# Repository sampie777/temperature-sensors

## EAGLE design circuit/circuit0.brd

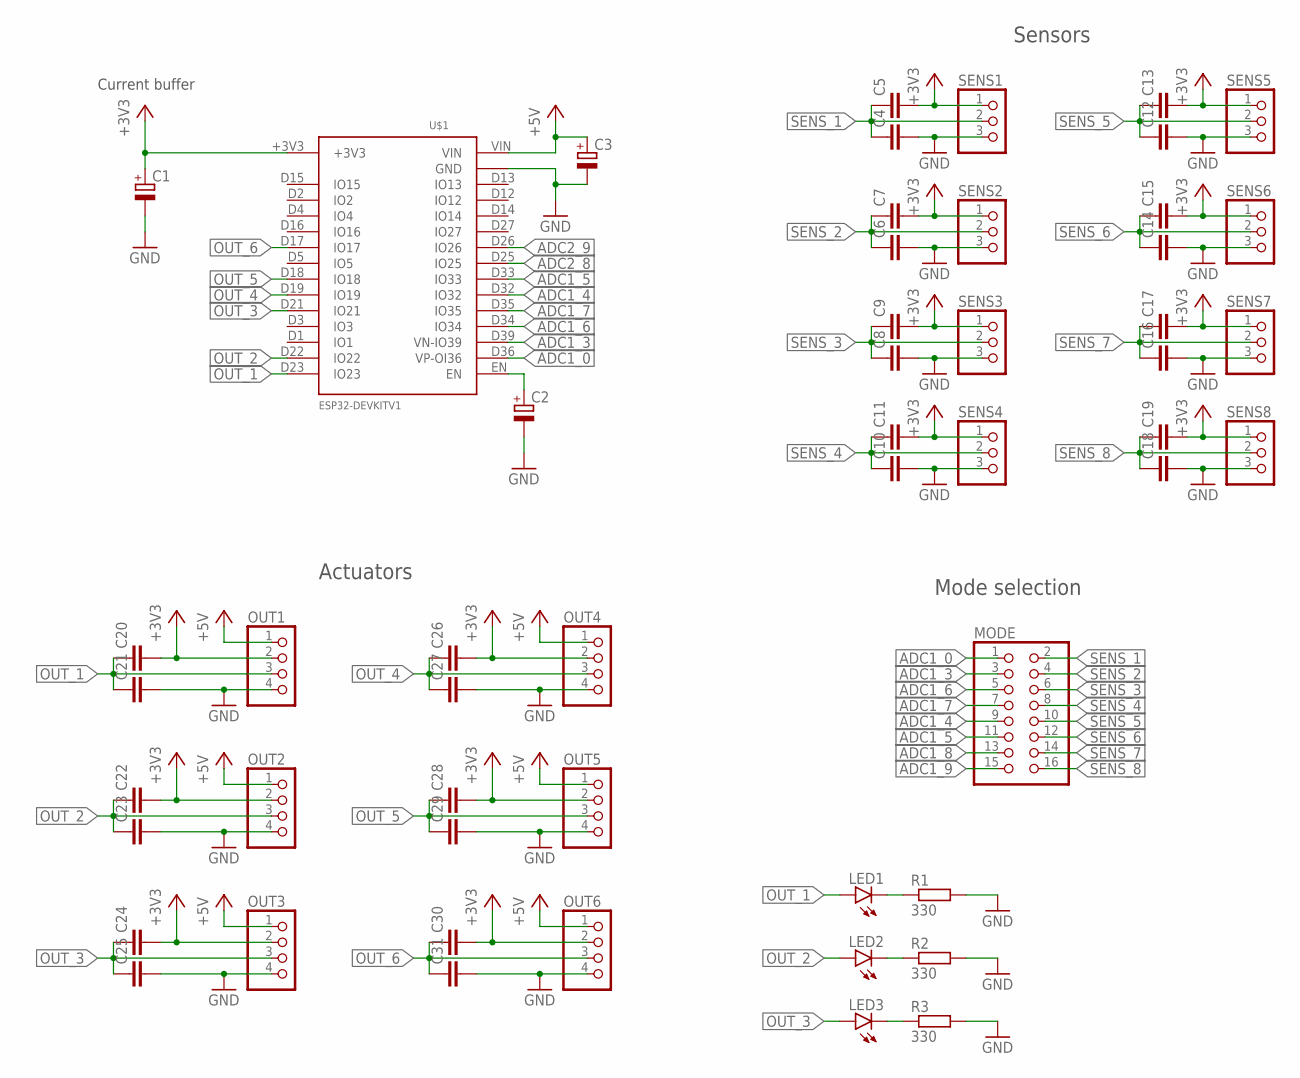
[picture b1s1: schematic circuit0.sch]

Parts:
C1, C2, C3: CPOL-EUE3.5-8; E3,5-8
C4, C5, C6, C7, C8, C9, C10, C11, C12, C13, C14, C15, C16, C17, C18, C19, C20, C21, C22, C23, C24, C25, C26, C27, C28, C29, C30, C31: C-EU025-030X050; C025-030X050
LED1, LED2, LED3: LED3MM
MODE: PINHD-2X8; 2X08
OUT1, OUT2, OUT3, OUT4, OUT5, OUT6: PINHD-1X4; 1X04
R1, R2, R3: 330; 0204/7
SENS1, SENS2, SENS3, SENS4, SENS5, SENS6, SENS7, SENS8: PINHD-1X3; 1X03
U$1: ESP32DEVKITV1; ESP32-DEVKITV1

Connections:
+3V3: C1.+, C5.2, C7.2, C9.2, C11.2, C13.2, C15.2, C17.2, C19.2, C20.2, C22.2, C24.2, C26.2, C28.2, C30.2, OUT1.2, OUT2.2, OUT3.2, OUT4.2, OUT5.2, OUT6.2, SENS1.1, SENS2.1, SENS3.1, SENS4.1, SENS5.1, SENS6.1, SENS7.1, SENS8.1, U$1.+3V3
+5V: C3.+, OUT1.1, OUT2.1, OUT3.1, OUT4.1, OUT5.1, OUT6.1, U$1.VIN
ADC1_0: MODE.1, U$1.D36 (VP-OI36)
ADC1_3: MODE.3, U$1.D39 (VN-IO39)
ADC1_4: MODE.9, U$1.D32 (IO32)
ADC1_5: MODE.11, U$1.D33 (IO33)
ADC1_6: MODE.5, U$1.D34 (IO34)
ADC1_7: MODE.7, U$1.D35 (IO35)
ADC1_8: MODE.13
ADC1_9: MODE.15
ADC2_8: U$1.D25 (IO25)
ADC2_9: U$1.D26 (IO26)
GND: C1.-, C2.-, C3.-, C4.2, C6.2, C8.2, C10.2, C12.2, C14.2, C16.2, C18.2, C21.2, C23.2, C25.2, C27.2, C29.2, C31.2, OUT1.4, OUT2.4, OUT3.4, OUT4.4, OUT5.4, OUT6.4, R1.2, R2.2, R3.2, SENS1.3, SENS2.3, SENS3.3, SENS4.3, SENS5.3, SENS6.3, SENS7.3, SENS8.3, U$1.GND, U$1.GND@2 (GND)
unnamed: C2.+, U$1.EN
unnamed: LED1.K (C), R1.1
unnamed: LED2.K (C), R2.1
unnamed: LED3.K (C), R3.1
OUT_1: C20.1, C21.1, LED1.A, OUT1.3, U$1.D23 (IO23)
OUT_2: C22.1, C23.1, LED2.A, OUT2.3, U$1.D22 (IO22)
OUT_3: C24.1, C25.1, LED3.A, OUT3.3, U$1.D21 (IO21)
OUT_4: C26.1, C27.1, OUT4.3, U$1.D19 (IO19)
OUT_5: C28.1, C29.1, OUT5.3, U$1.D18 (IO18)
OUT_6: C30.1, C31.1, OUT6.3, U$1.D17 (IO17)
SENS_1: C4.1, C5.1, MODE.2, SENS1.2
SENS_2: C6.1, C7.1, MODE.4, SENS2.2
SENS_3: C8.1, C9.1, MODE.6, SENS3.2
SENS_4: C10.1, C11.1, MODE.8, SENS4.2
SENS_5: C12.1, C13.1, MODE.10, SENS5.2
SENS_6: C14.1, C15.1, MODE.12, SENS6.2
SENS_7: C16.1, C17.1, MODE.14, SENS7.2
SENS_8: C18.1, C19.1, MODE.16, SENS8.2

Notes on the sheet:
Current buffer
Mode selection
Sensors
Actuators

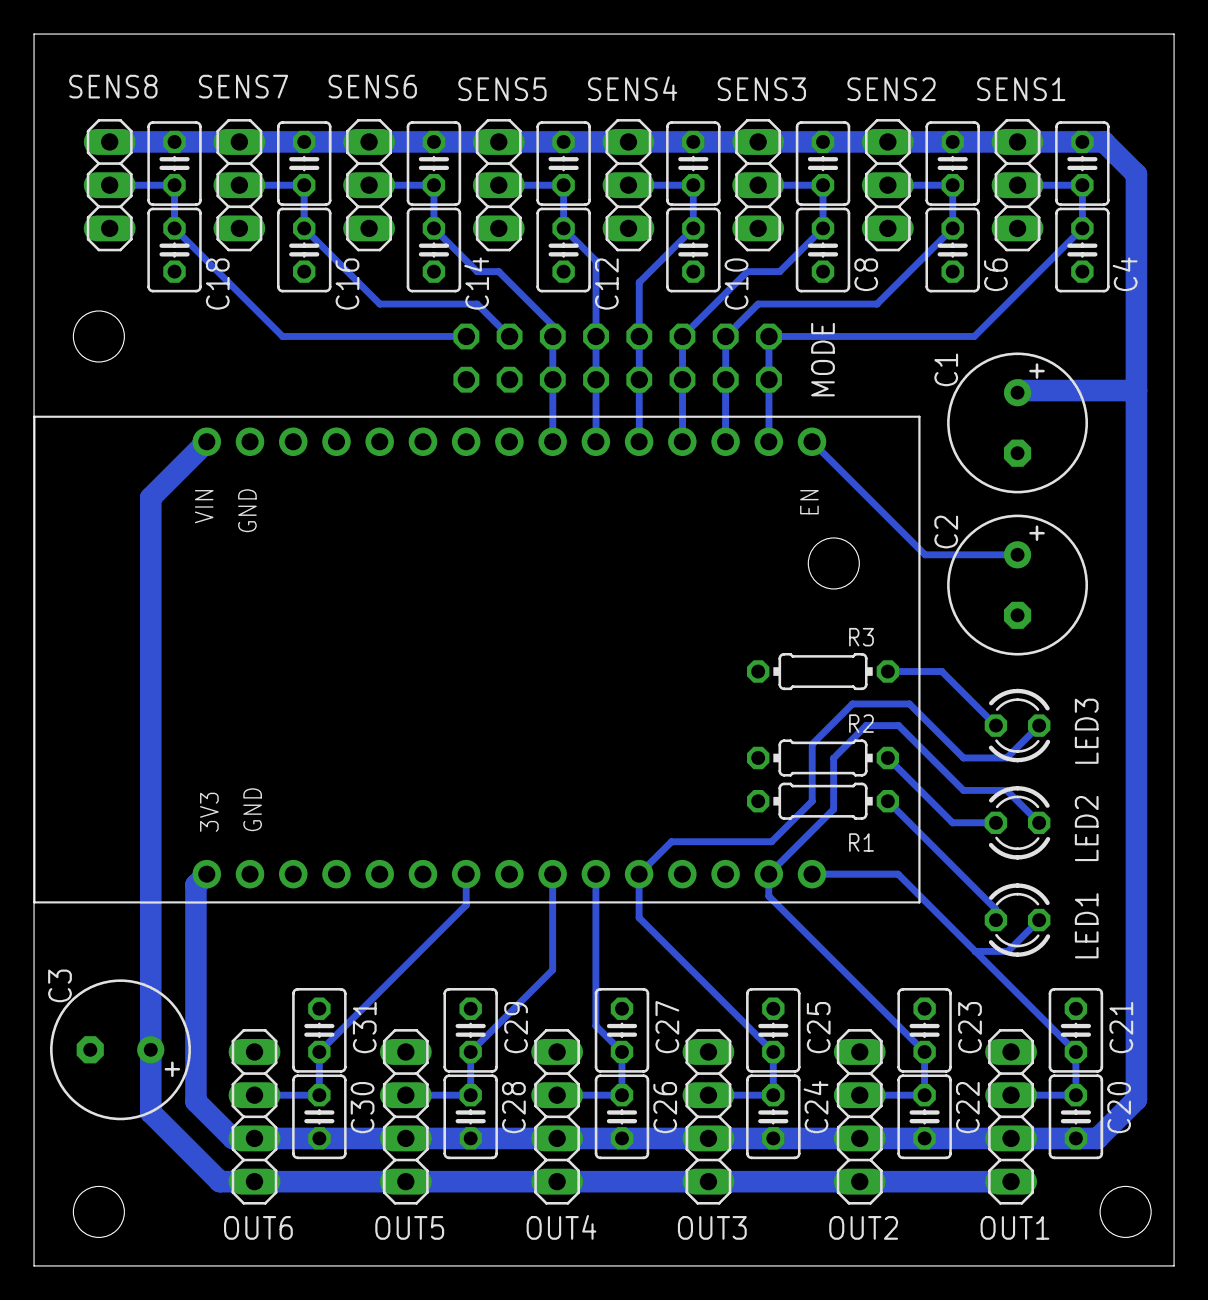
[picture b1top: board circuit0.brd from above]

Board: 2 copper layers, 67.0 x 72.4 mm, 53 parts (1 on the bottom side), 27 nets.

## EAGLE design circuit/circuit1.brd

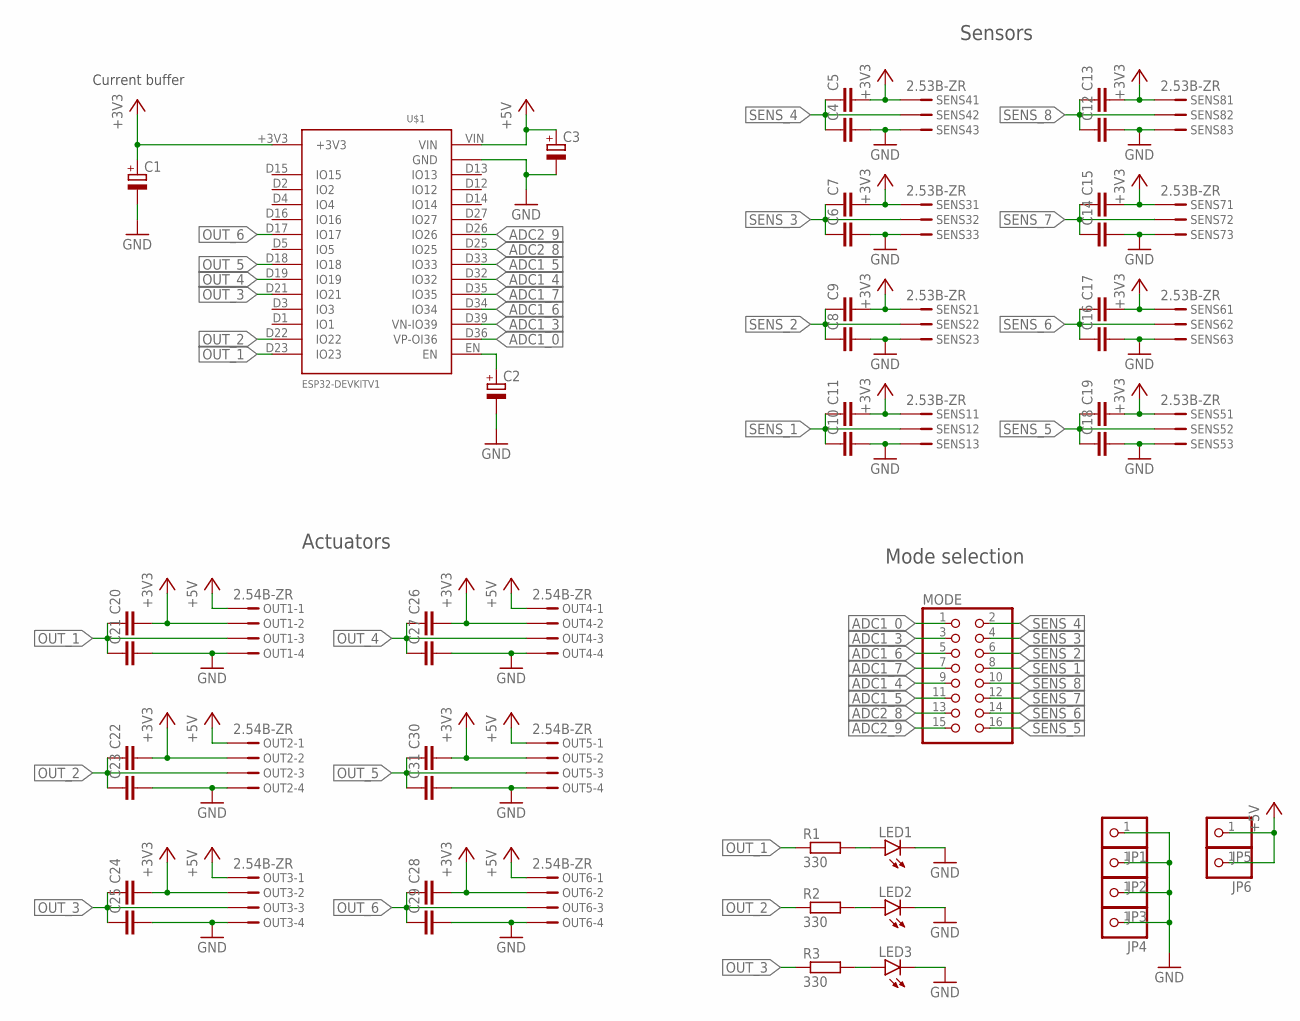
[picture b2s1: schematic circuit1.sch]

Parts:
C1, C2, C3: CPOL-EUE3.5-8; E3,5-8
C4, C5, C6, C7, C8, C9, C10, C11, C12, C13, C14, C15, C16, C17, C18, C19, C20, C21, C22, C23, C24, C25, C26, C27, C28, C29, C30, C31: C-EU025-030X050; C025-030X050
JP1, JP2, JP3, JP4, JP5, JP6: PINHD-1X1; 1X01
LED1, LED2, LED3: LED3MM
MODE: PINHD-2X8; 2X08
OUT1, OUT2, OUT3, OUT4, OUT5, OUT6: 2.54B-ZR; B4B-ZR2.5
R1, R2, R3: 330; 0204/7
SENS1, SENS2, SENS3, SENS4, SENS5, SENS6, SENS7, SENS8: 2.53B-ZR; B3B-ZR2.5
U$1: ESP32DEVKITV1; ESP32-DEVKITV1

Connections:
+3V3: C1.+, C5.2, C7.2, C9.2, C11.2, C13.2, C15.2, C17.2, C19.2, C20.2, C22.2, C24.2, C26.2, C28.2, C30.2, OUT1.2, OUT2.2, OUT3.2, OUT4.2, OUT5.2, OUT6.2, SENS1.1, SENS2.1, SENS3.1, SENS4.1, SENS5.1, SENS6.1, SENS7.1, SENS8.1, U$1.+3V3
+5V: C3.+, JP5.1, JP6.1, OUT1.1, OUT2.1, OUT3.1, OUT4.1, OUT5.1, OUT6.1, U$1.VIN
ADC1_0: MODE.1, U$1.D36 (VP-OI36)
ADC1_3: MODE.3, U$1.D39 (VN-IO39)
ADC1_4: MODE.9, U$1.D32 (IO32)
ADC1_5: MODE.11, U$1.D33 (IO33)
ADC1_6: MODE.5, U$1.D34 (IO34)
ADC1_7: MODE.7, U$1.D35 (IO35)
ADC2_8: MODE.13, U$1.D25 (IO25)
ADC2_9: MODE.15, U$1.D26 (IO26)
GND: C1.-, C2.-, C3.-, C4.2, C6.2, C8.2, C10.2, C12.2, C14.2, C16.2, C18.2, C21.2, C23.2, C25.2, C27.2, C29.2, C31.2, JP1.1, JP2.1, JP3.1, JP4.1, LED1.K (C), LED2.K (C), LED3.K (C), OUT1.4, OUT2.4, OUT3.4, OUT4.4, OUT5.4, OUT6.4, SENS1.3, SENS2.3, SENS3.3, SENS4.3, SENS5.3, SENS6.3, SENS7.3, SENS8.3, U$1.GND, U$1.GND@2 (GND)
unnamed: C2.+, U$1.EN
unnamed: LED1.A, R1.2
unnamed: LED2.A, R2.2
unnamed: LED3.A, R3.2
OUT_1: C20.1, C21.1, OUT1.3, R1.1, U$1.D23 (IO23)
OUT_2: C22.1, C23.1, OUT2.3, R2.1, U$1.D22 (IO22)
OUT_3: C24.1, C25.1, OUT3.3, R3.1, U$1.D21 (IO21)
OUT_4: C26.1, C27.1, OUT4.3, U$1.D19 (IO19)
OUT_5: C30.1, C31.1, OUT5.3, U$1.D18 (IO18)
OUT_6: C28.1, C29.1, OUT6.3, U$1.D17 (IO17)
SENS_1: C10.1, C11.1, MODE.8, SENS1.2
SENS_2: C8.1, C9.1, MODE.6, SENS2.2
SENS_3: C6.1, C7.1, MODE.4, SENS3.2
SENS_4: C4.1, C5.1, MODE.2, SENS4.2
SENS_5: C18.1, C19.1, MODE.16, SENS5.2
SENS_6: C16.1, C17.1, MODE.14, SENS6.2
SENS_7: C14.1, C15.1, MODE.12, SENS7.2
SENS_8: C12.1, C13.1, MODE.10, SENS8.2

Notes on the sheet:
Current buffer
Mode selection
Sensors
Actuators

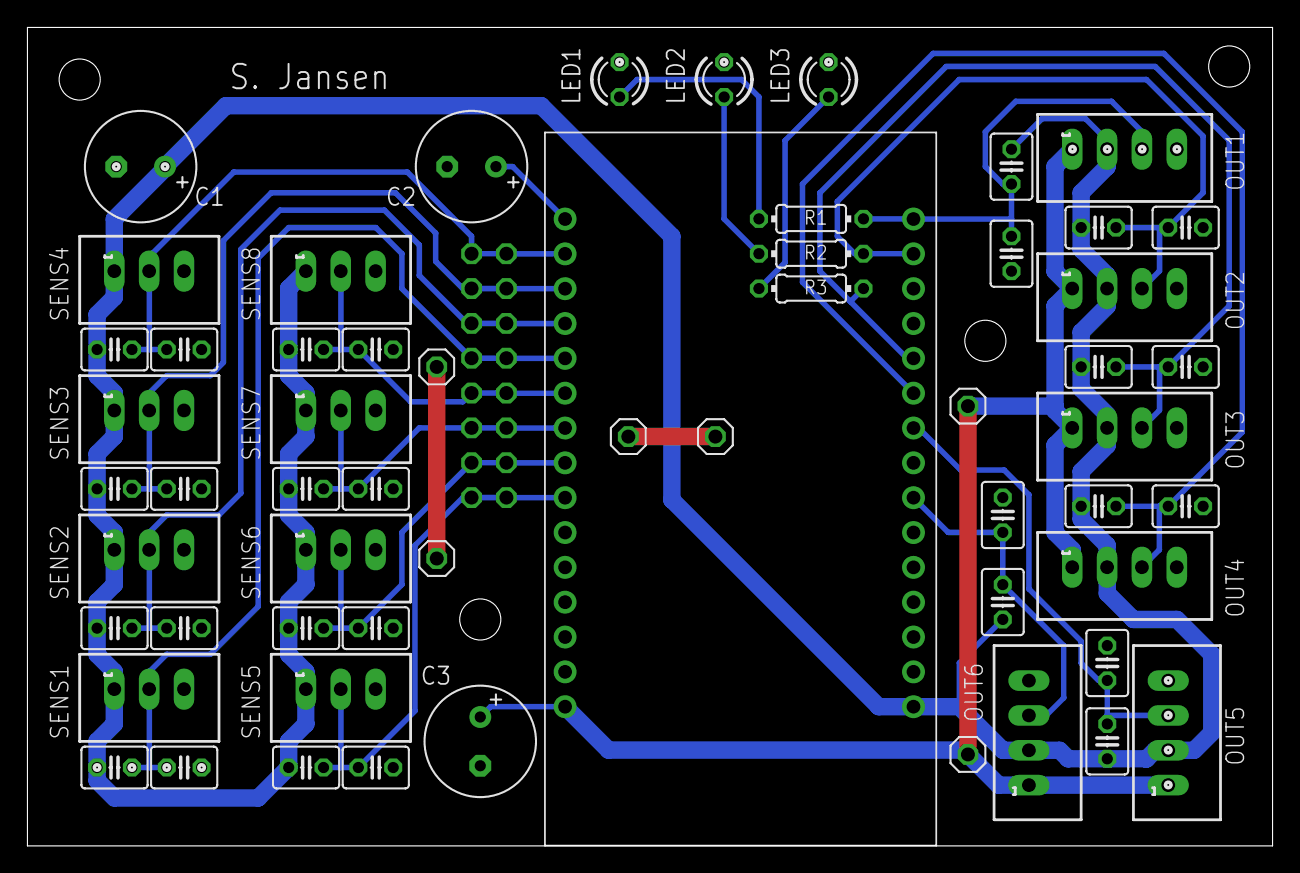
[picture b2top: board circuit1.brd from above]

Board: 2 copper layers, 90.8 x 59.7 mm, 59 parts (1 on the bottom side), 29 nets.

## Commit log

2024-07-13 Project init
2024-07-13 Secondary circuit finished
